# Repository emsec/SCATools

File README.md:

SCATools
========

Open tools for side-channel analysis and related techniques. 

All information can be found in the [project wiki](https://github.com/emsec/SCATools/wiki)

Currently, this repository contains: 

1) A near-field EM probe amplifier circuit: [building guide in wiki](https://github.com/emsec/SCATools/wiki/BuildEMProbe)

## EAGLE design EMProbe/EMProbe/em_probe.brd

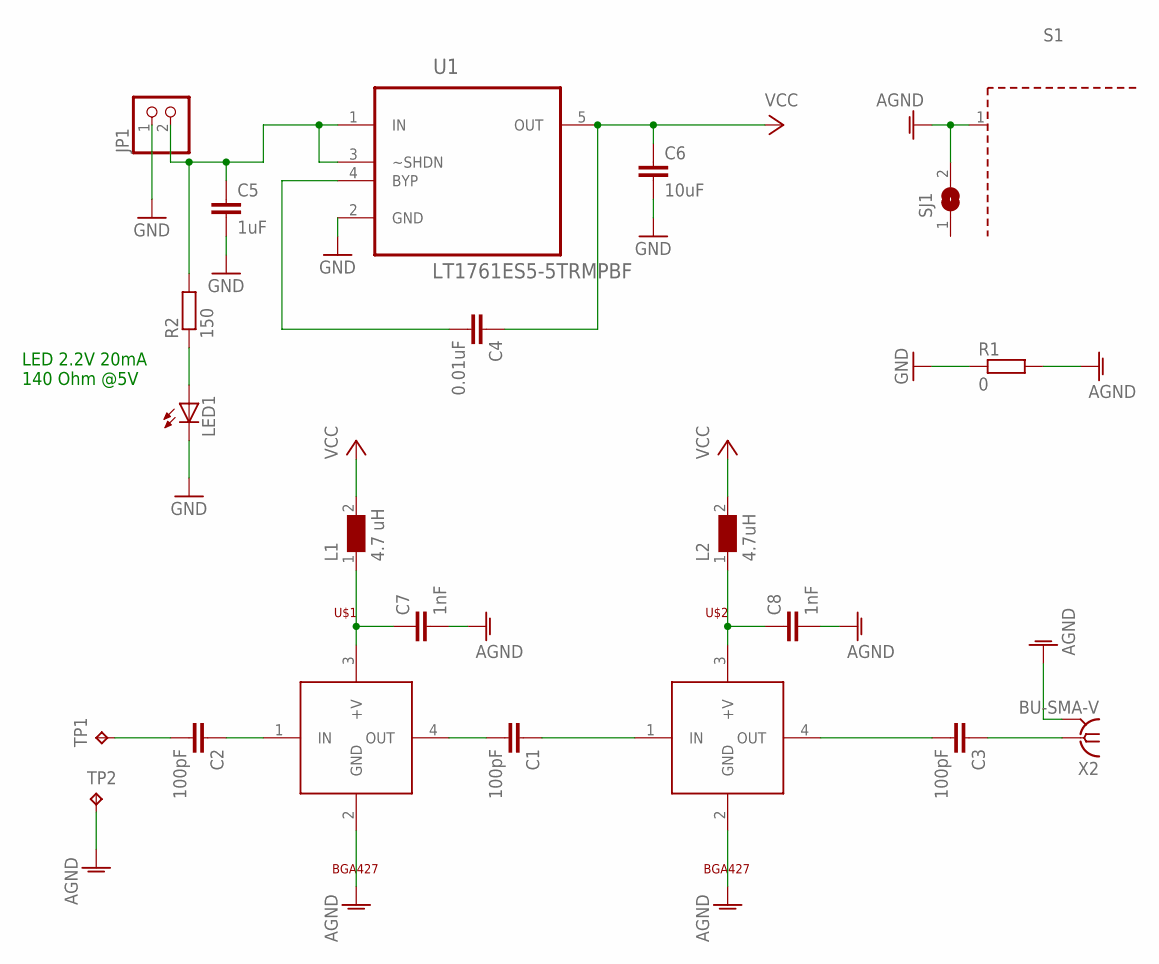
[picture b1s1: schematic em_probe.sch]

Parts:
C1, C2, C3: 100pF; C0805
C4: 0.01uF; C0805
C5: 1uF; C0805
C6: 10uF; C0805
C7, C8: 1nF; C0805
JP1: PINHD-1X2/90; 1X02/90
L1: 4.7 uH; WE-RFH
L2: 4.7uH; WE-RFH
LED1: LEDCHIPLED_0805; CHIPLED_0805
R1: 0; R0805
R2: 150; R0805
S1: WE-SHC_36103305
SJ1: SJ
TP1, TP2: TPTP15R; TP15R
U1: LT1761ES5-5TRMPBF; SOT95P280X100-5N
U$1, U$2: BGA427; SOT343
X2: BU-SMA-V

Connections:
AGND: C7.2, C8.2, R1.2, S1.1, SJ1.2, TP2.TP, U$1.2 (GND), U$2.2 (GND), X2.2, X2.3 (2), X2.4 (2), X2.5 (2)
GND: C5.2, C6.2, JP1.1, LED1.C, R1.1, U1.2 (GND)
unnamed: C2.1, U$1.1 (IN)
unnamed: C1.2, U$1.4 (OUT)
unnamed: C1.1, U$2.1 (IN)
unnamed: C3.2, U$2.4 (OUT)
unnamed: C3.1, X2.1
unnamed: C5.1, JP1.2, R2.2, U1.1 (IN), U1.3 (~SHDN)
unnamed: C4.2, U1.4 (BYP)
unnamed: C2.2, TP1.TP
unnamed: C7.1, L1.1, U$1.3 (+V)
unnamed: C8.1, L2.1, U$2.3 (+V)
unnamed: LED1.A, R2.1
VCC: C4.1, C6.1, L1.2, L2.2, U1.5 (OUT)

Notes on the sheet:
LED 2.2V 20mA 140 Ohm @5V

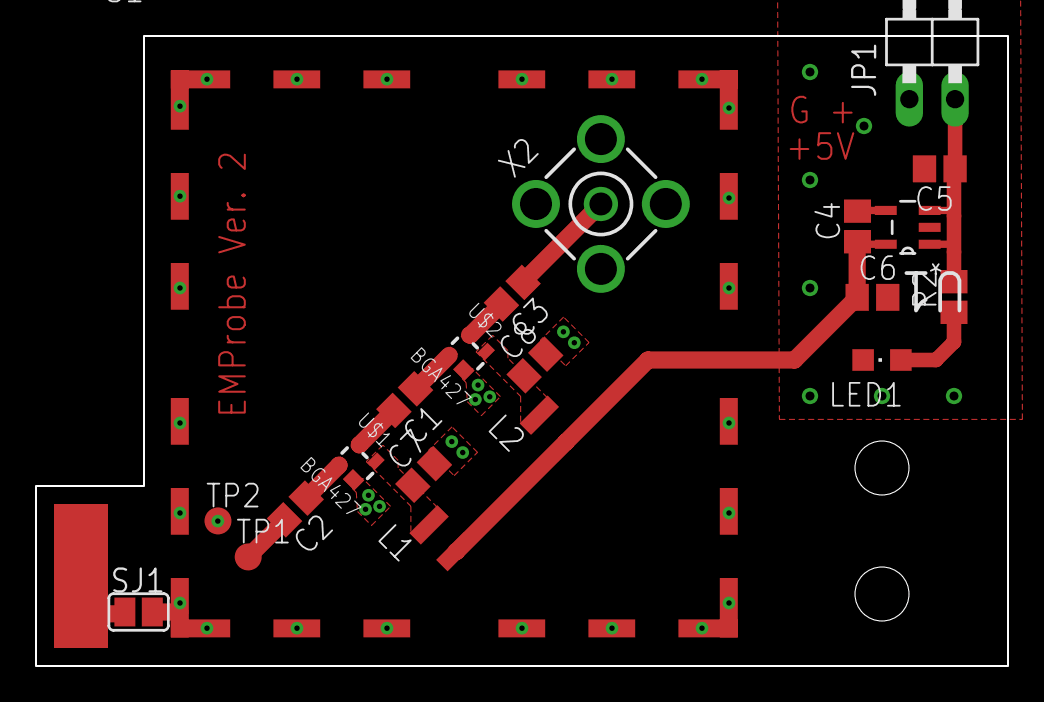
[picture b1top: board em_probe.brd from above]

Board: 2 copper layers, 54.0 x 35.0 mm, 22 parts (1 on the bottom side), 14 nets.

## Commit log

2014-11-24 Create LICENSE
2014-11-28 PCB and schematics
2014-12-15 Pictures for build howto
2014-12-15 Removed . in filename
2014-12-17 Added PDF schematics
